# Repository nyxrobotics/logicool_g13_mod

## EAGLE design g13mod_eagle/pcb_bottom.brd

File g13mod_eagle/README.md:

[clueboard/eagle_libs](https://github.com/clueboard/eagle_libs/blob/master/Keyboard.lbr)

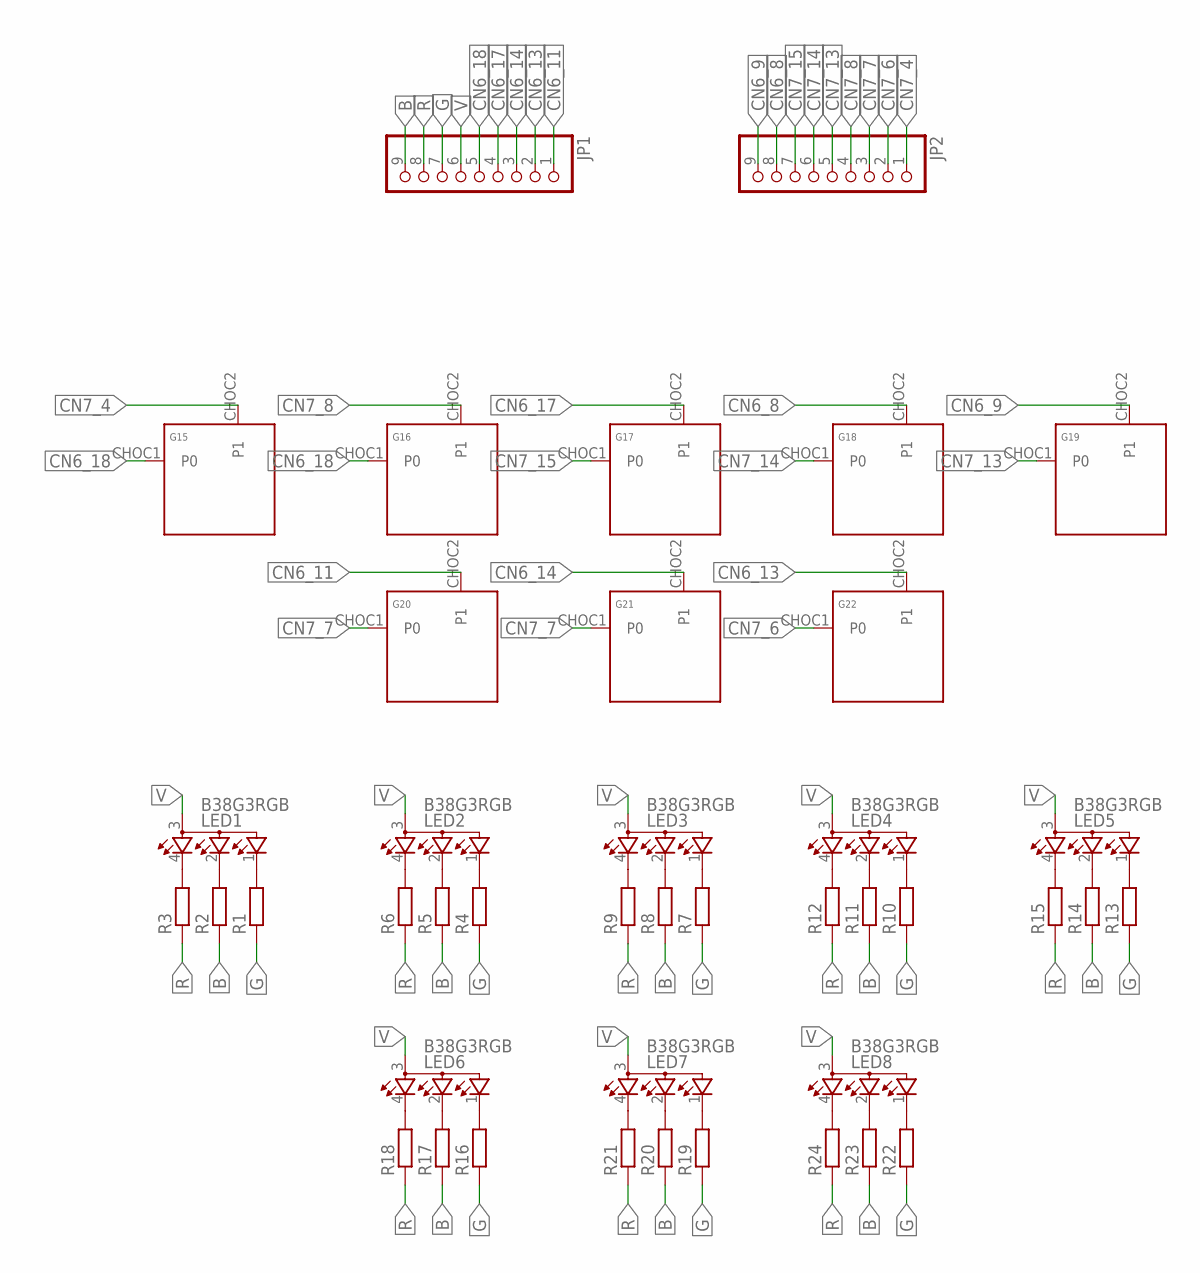
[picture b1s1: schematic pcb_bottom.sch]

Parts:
G15, G16, G17, G18, G19, G20, G21, G22: KEYSWITCH-PLAIN-CHOC-1U; CHOC-1U
JP1, JP2: THROUHOLE09
LED1, LED2, LED3, LED4, LED5, LED6, LED7, LED8: B38G3RGB
R1, R2, R3, R4, R5, R6, R7, R8, R9, R10, R11, R12, R13, R14, R15, R16, R17, R18, R19, R20, R21, R22, R23, R24: R-EU_R0603; R0603

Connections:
B: JP1.9, R2.1, R5.1, R8.1, R11.1, R14.1, R17.1, R20.1, R23.1
CN6_8: G18.CHOC2 (P1), JP2.8
CN6_9: G19.CHOC2 (P1), JP2.9
CN6_11: G20.CHOC2 (P1), JP1.1
CN6_13: G22.CHOC2 (P1), JP1.2
CN6_14: G21.CHOC2 (P1), JP1.3
CN6_17: G17.CHOC2 (P1), JP1.4
CN6_18: G15.CHOC1 (P0), G16.CHOC1 (P0), JP1.5
CN7_4: G15.CHOC2 (P1), JP2.1
CN7_6: G22.CHOC1 (P0), JP2.2
CN7_7: G20.CHOC1 (P0), G21.CHOC1 (P0), JP2.3
CN7_8: G16.CHOC2 (P1), JP2.4
CN7_13: G19.CHOC1 (P0), JP2.5
CN7_14: G18.CHOC1 (P0), JP2.6
CN7_15: G17.CHOC1 (P0), JP2.7
G: JP1.7, R1.1, R4.1, R7.1, R10.1, R13.1, R16.1, R19.1, R22.1
unnamed: LED1.1 (CGREEN), R1.2
unnamed: LED1.2 (CBLUE), R2.2
unnamed: LED1.4 (CRED), R3.2
unnamed: LED2.1 (CGREEN), R4.2
unnamed: LED2.2 (CBLUE), R5.2
unnamed: LED2.4 (CRED), R6.2
unnamed: LED3.1 (CGREEN), R7.2
unnamed: LED3.2 (CBLUE), R8.2
unnamed: LED3.4 (CRED), R9.2
unnamed: LED4.1 (CGREEN), R10.2
unnamed: LED4.2 (CBLUE), R11.2
unnamed: LED4.4 (CRED), R12.2
unnamed: LED5.1 (CGREEN), R13.2
unnamed: LED5.2 (CBLUE), R14.2
unnamed: LED5.4 (CRED), R15.2
unnamed: LED6.1 (CGREEN), R16.2
unnamed: LED6.2 (CBLUE), R17.2
unnamed: LED6.4 (CRED), R18.2
unnamed: LED7.1 (CGREEN), R19.2
unnamed: LED7.2 (CBLUE), R20.2
unnamed: LED7.4 (CRED), R21.2
unnamed: LED8.1 (CGREEN), R22.2
unnamed: LED8.2 (CBLUE), R23.2
unnamed: LED8.4 (CRED), R24.2
R: JP1.8, R3.1, R6.1, R9.1, R12.1, R15.1, R18.1, R21.1, R24.1
V: JP1.6, LED1.3 (A), LED2.3 (A), LED3.3 (A), LED4.3 (A), LED5.3 (A), LED6.3 (A), LED7.3 (A), LED8.3 (A)

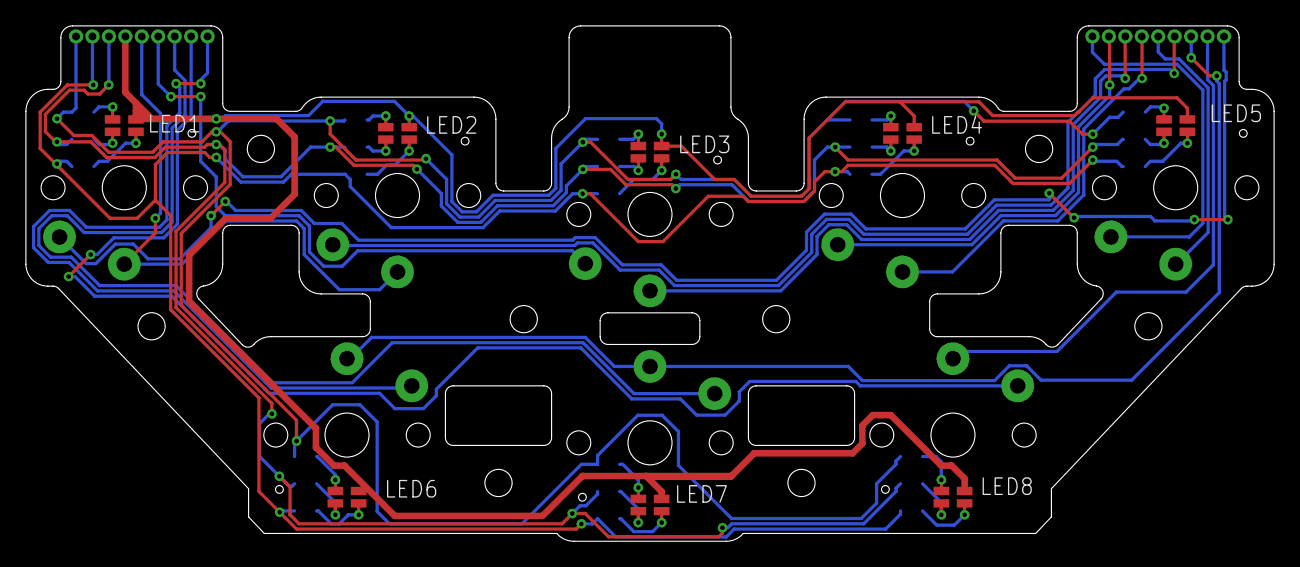
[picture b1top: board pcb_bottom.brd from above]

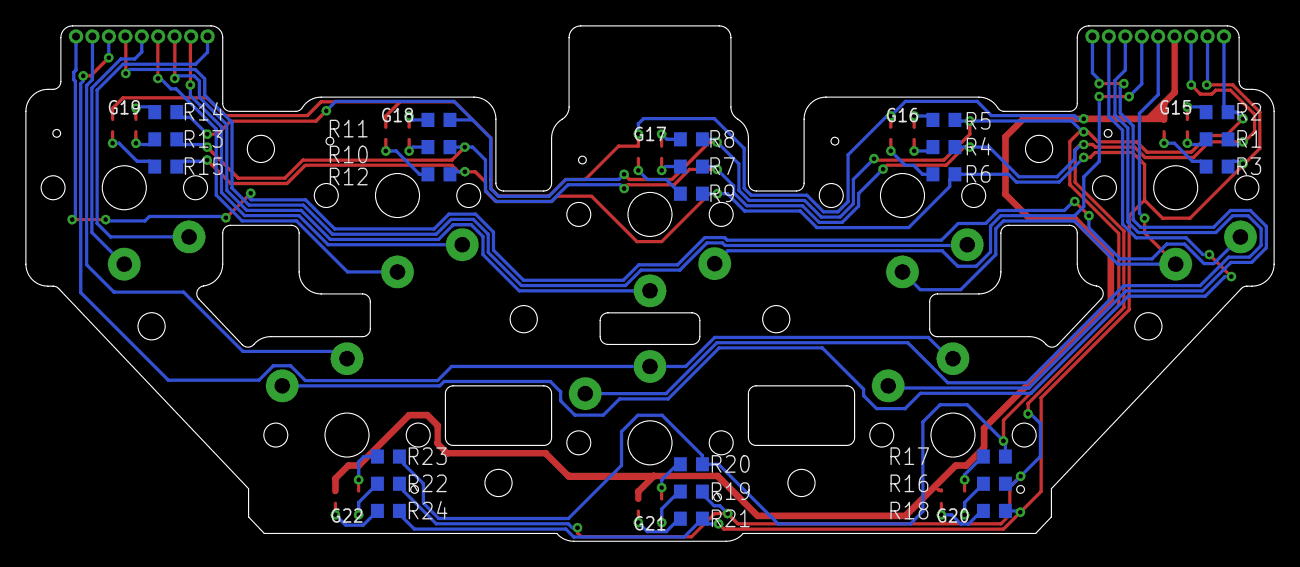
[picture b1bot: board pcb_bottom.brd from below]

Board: 2 copper layers, 96.4 x 39.8 mm, 42 parts (24 on the bottom side), 42 nets.

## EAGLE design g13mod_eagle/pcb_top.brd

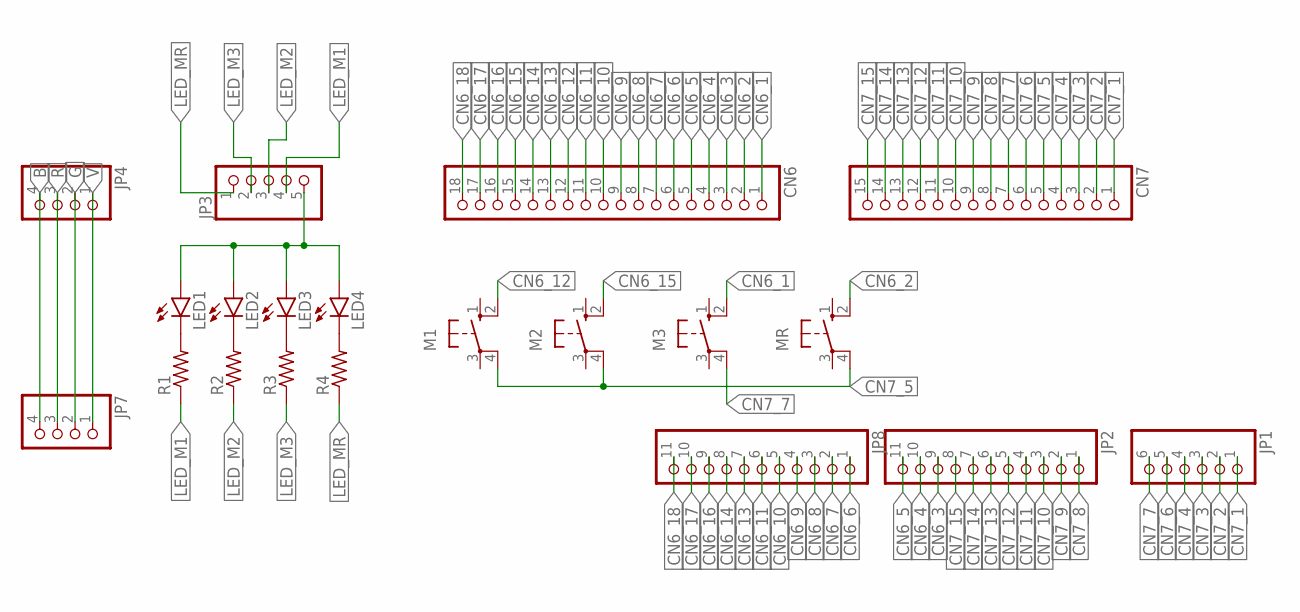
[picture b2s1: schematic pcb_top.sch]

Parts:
CN6: THROUHOLE18
CN7: THROUHOLE15
JP1: THROUHOLE06
JP2, JP8: THROUHOLE11
JP3: THROUHOLE05
JP4, JP7: THROUHOLE04
LED1, LED2, LED3, LED4: LEDCHIPLED_1206; CHIPLED_1206
M1, M2, M3: 10-XX; B3F-10XX
MR: 10-XX; B3F-10XX
R1, R2, R3, R4: R-US_R0603; R0603

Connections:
B: JP4.4, JP7.4
CN6_1: CN6.1, M3.2 (S1)
CN6_2: CN6.2, MR.2 (S1)
CN6_3: CN6.3, JP2.9
CN6_4: CN6.4, JP2.10
CN6_5: CN6.5, JP2.11
CN6_6: CN6.6, JP8.1
CN6_7: CN6.7, JP8.2
CN6_8: CN6.8, JP8.3
CN6_9: CN6.9, JP8.4
CN6_10: CN6.10, JP8.5
CN6_11: CN6.11, JP8.6
CN6_12: CN6.12, M1.2 (S1)
CN6_13: CN6.13, JP8.7
CN6_14: CN6.14, JP8.8
CN6_15: CN6.15, M2.2 (S1)
CN6_16: CN6.16, JP8.9
CN6_17: CN6.17, JP8.10
CN6_18: CN6.18, JP8.11
CN7_1: CN7.1, JP1.1
CN7_2: CN7.2, JP1.2
CN7_3: CN7.3, JP1.3
CN7_4: CN7.4, JP1.4
CN7_5: CN7.5, M1.4 (P1), M2.4 (P1), MR.4 (P1)
CN7_6: CN7.6, JP1.5
CN7_7: CN7.7, JP1.6, M3.4 (P1)
CN7_8: CN7.8, JP2.1
CN7_9: CN7.9, JP2.2
CN7_10: CN7.10, JP2.3
CN7_11: CN7.11, JP2.4
CN7_12: CN7.12, JP2.5
CN7_13: CN7.13, JP2.6
CN7_14: CN7.14, JP2.7
CN7_15: CN7.15, JP2.8
G: JP4.2, JP7.2
LED_M1: JP3.4, R1.1
LED_M2: JP3.3, R2.1
LED_M3: JP3.2, R3.1
LED_MR: JP3.1, R4.1
unnamed: JP3.5, LED1.A, LED2.A, LED3.A, LED4.A
unnamed: LED1.C, R1.2
unnamed: LED2.C, R2.2
unnamed: LED3.C, R3.2
unnamed: LED4.C, R4.2
R: JP4.3, JP7.3
V: JP4.1, JP7.1

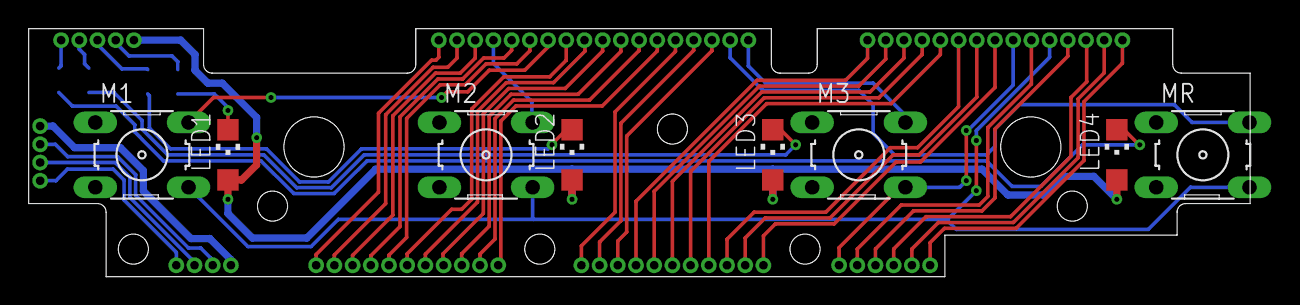
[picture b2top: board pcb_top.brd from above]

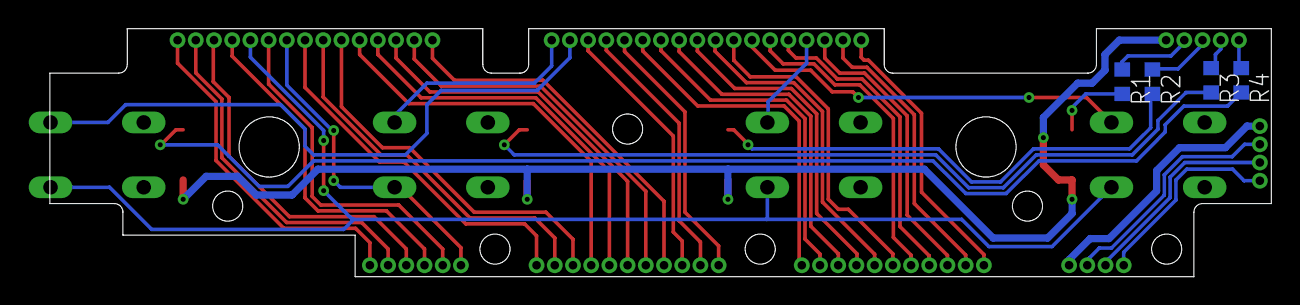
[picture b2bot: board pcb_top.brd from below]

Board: 2 copper layers, 85.2 x 17.3 mm, 20 parts (4 on the bottom side), 46 nets.

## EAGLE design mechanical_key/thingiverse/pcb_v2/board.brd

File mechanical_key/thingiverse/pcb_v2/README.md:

### Library
- [Cherrymx](https://www.diymodules.org/eagle-show-library?type=usr&id=1012211733)
	- Move "dimension" layer drawings to "tPlace"

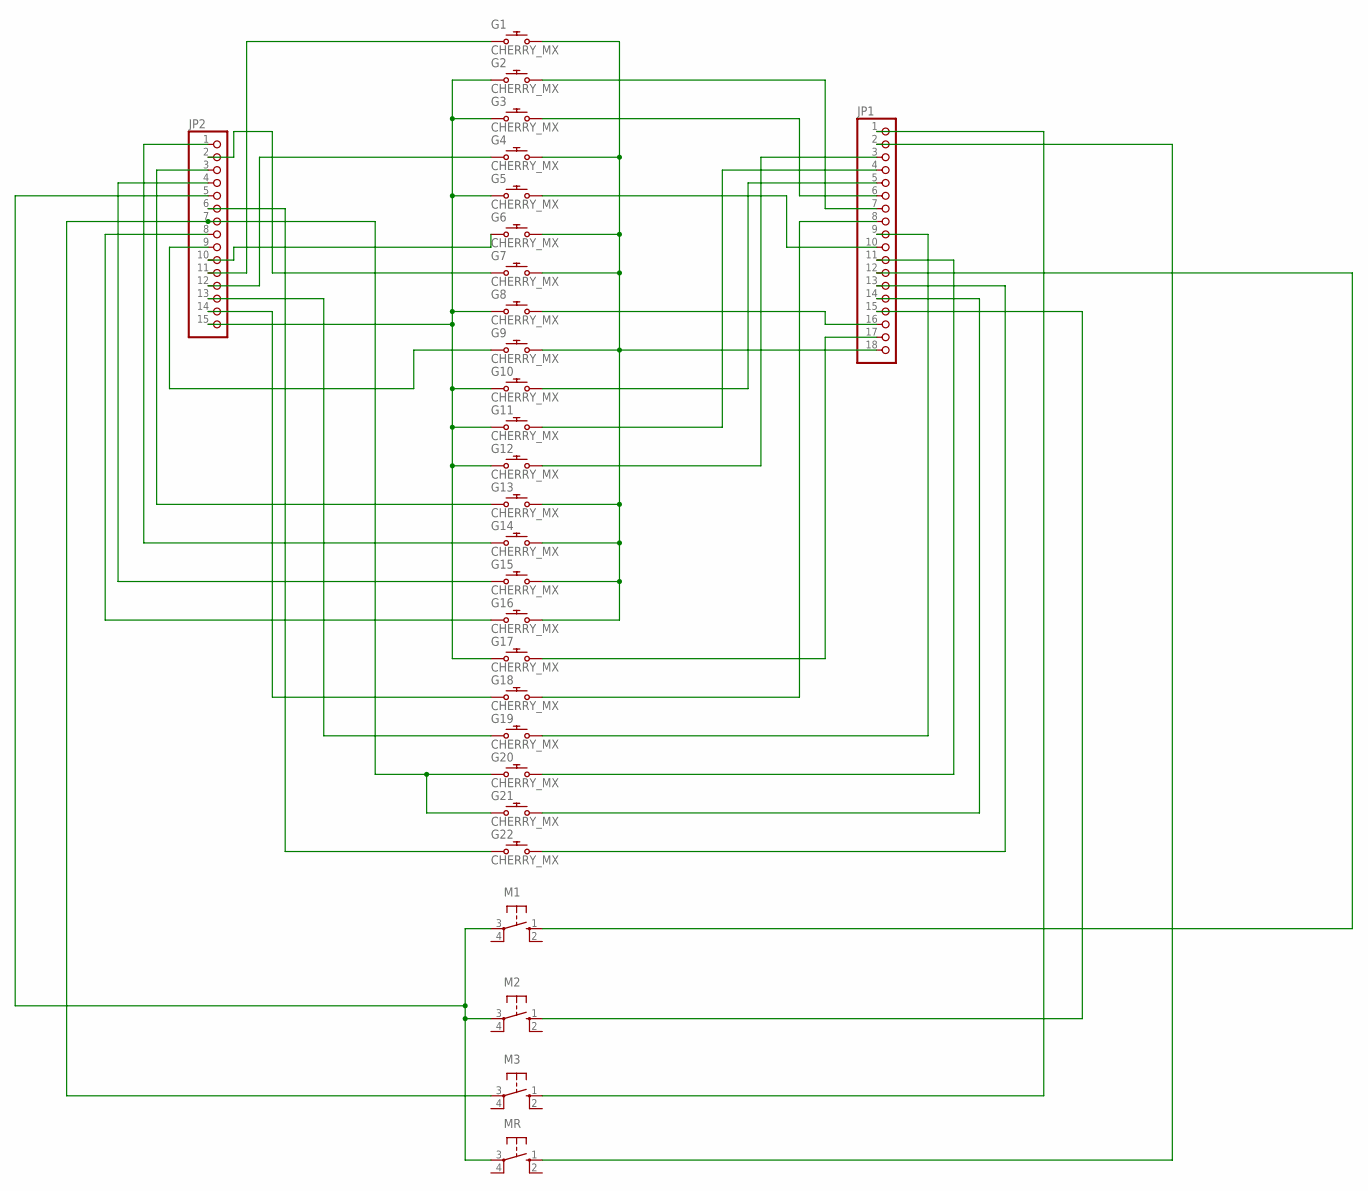
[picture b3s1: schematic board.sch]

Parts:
G1, G2, G3, G4, G5, G6, G7, G8, G9, G10, G11, G12, G13, G14, G15, G16, G17, G18, G19, G20, G21, G22: CHERRY_MX
JP1: PINHD-1X18/90; 1X18/90
JP2: PINHD-1X15/90; 1X15/90
M1, M2, M3: 10-XX; B3F-10XX
MR: 10-XX; B3F-10XX

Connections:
unnamed: G2.S1 (1), G3.S1 (1), G5.S1 (1), G8.S1 (1), G10.S1 (1), G11.S1 (1), G12.S1 (1), G17.S1 (1), JP2.15
unnamed: G6.S1 (1), JP2.10
unnamed: G1.S1 (1), JP2.11
unnamed: G4.S1 (1), JP2.12
unnamed: G7.S1 (1), JP2.2
unnamed: G13.S1 (1), JP2.3
unnamed: G9.S1 (1), JP2.9
unnamed: G14.S1 (1), JP2.1
unnamed: G15.S1 (1), JP2.4
unnamed: G16.S1 (1), JP2.8
unnamed: G18.S1 (1), JP2.14
unnamed: G19.S1 (1), JP2.13
unnamed: G20.S1 (1), G21.S1 (1), JP2.7, M3.3
unnamed: G11.S2 (2), JP1.4
unnamed: G22.S1 (1), JP2.6
unnamed: G1.S2 (2), G4.S2 (2), G6.S2 (2), G7.S2 (2), G9.S2 (2), G13.S2 (2), G14.S2 (2), G15.S2 (2), G16.S2 (2), JP1.18
unnamed: G2.S2 (2), JP1.7
unnamed: G3.S2 (2), JP1.6
unnamed: G5.S2 (2), JP1.10
unnamed: G8.S2 (2), JP1.16
unnamed: G10.S2 (2), JP1.5
unnamed: G12.S2 (2), JP1.3
unnamed: G17.S2 (2), JP1.17
unnamed: G18.S2 (2), JP1.8
unnamed: G19.S2 (2), JP1.9
unnamed: G20.S2 (2), JP1.11
unnamed: G21.S2 (2), JP1.14
unnamed: G22.S2 (2), JP1.13
unnamed: JP2.5, M1.3, M2.3, MR.3
unnamed: JP1.1, M3.1 (S)
unnamed: JP1.2, MR.1 (S)
unnamed: JP1.15, M2.1 (S)
unnamed: JP1.12, M1.1 (S)

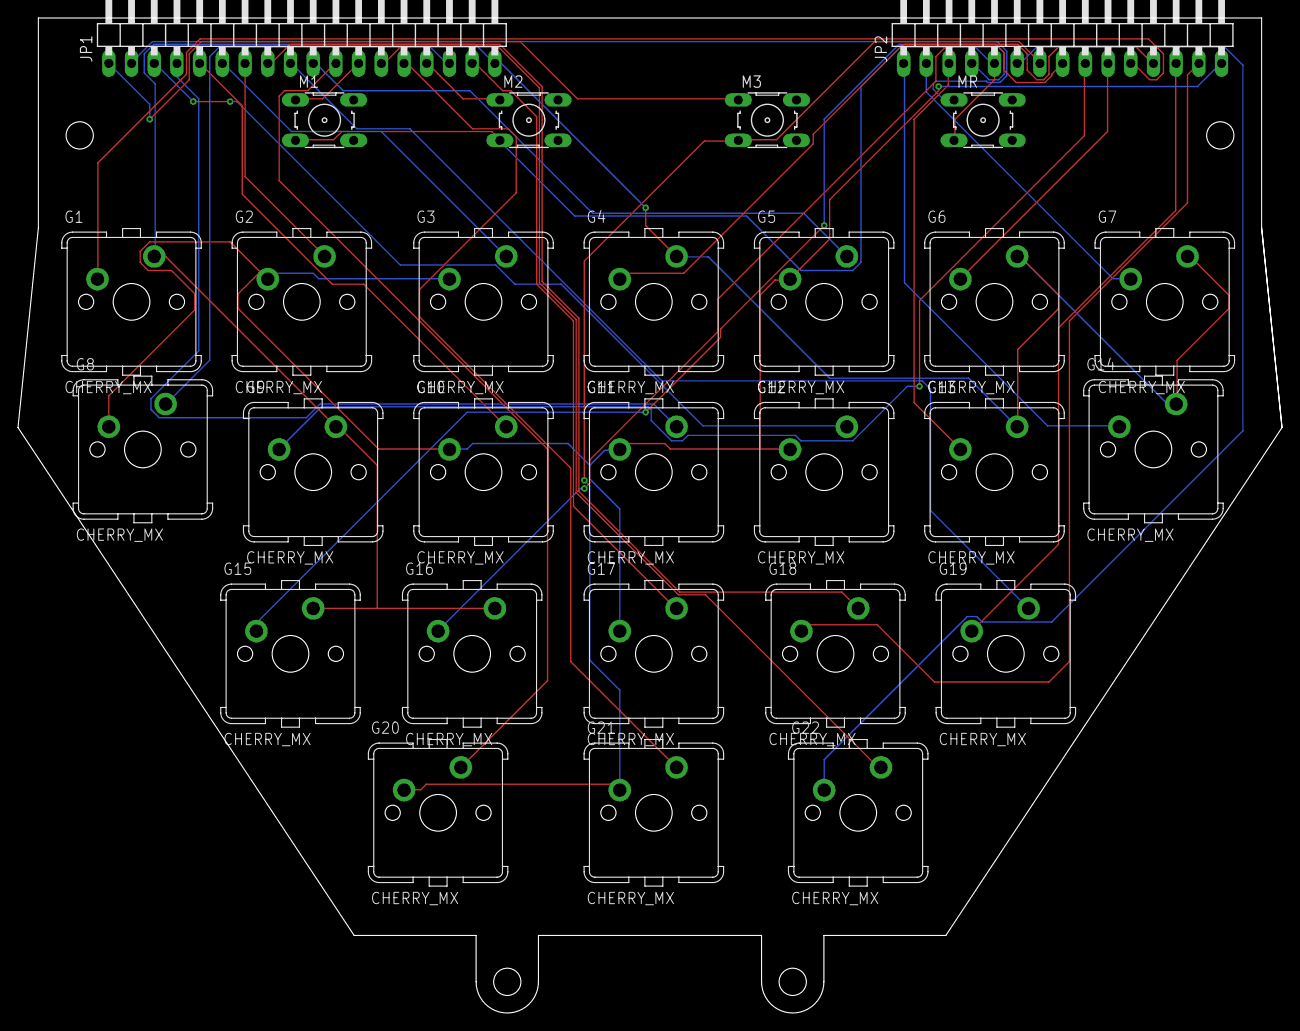
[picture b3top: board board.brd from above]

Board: 2 copper layers, 141.4 x 111.3 mm, 28 parts (0 on the bottom side), 33 nets.

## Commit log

2021-07-30 add files
2021-07-30 Add pcb data (Eagle)
2021-07-30 Add Cherry MX keys
2021-07-30 Generate pcb_v2 outline
2021-07-30 Add mechanical key mod files
2021-07-30 Add kailh mod
2021-07-30 1st test print
2021-07-31 ADD PLASTIC MOUNT
2021-07-31 UPDATE DESIGN
2021-07-31 round edges
2021-08-01 Fix shape
2021-08-01 Add menu switches
2021-08-01 Change holes
2021-08-01 Fix thickness
2021-08-01 Fix led
2021-08-04 edit holes
2021-08-08 Fix features
2021-08-08 Fix dimension
2021-08-08 Remove hidden features
2021-08-09 add wiring space
2021-08-09 update stl
2021-08-21 Avoid collision
2021-08-21 Fix bug
2021-08-22 Add offset
2021-10-17 Add pcb outline
2021-10-24 [Eagle] Create outline
2021-10-24 Fix bottom pcb
2021-10-30 Add switches
2021-10-30 wiring
2021-10-31 wiring top pcb
2021-10-31 Edit connector
2021-11-03 wiring middle pcb
2021-11-12 wiring bottom pcb
2021-11-14 Edit width
2021-11-30 Fix LED color
